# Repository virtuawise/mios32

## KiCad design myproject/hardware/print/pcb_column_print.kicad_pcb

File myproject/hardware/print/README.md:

# 1:1 test prints – check the real parts before ordering

Generated by `make_print_parts.py` (KiCad's Python) and `make_spacers.py` from the real board files, so every hole is
where the ordered PCBs will have it.

| File | What | Print |
|---|---|---|
| `pcb_left.stl`, `pcb_column.stl` | PCB stand-ins with all holes (switch pins, encoder lugs, LED, OLED header, stack holes) | 1.6 mm |
| `plate_left.stl`, `plate_column1.stl` | switch plate section | 1.6 mm as exported; **scale Z to 1.5 mm** (MX clips are made for 1.5) |
| `front_left.stl`, `front_column1.stl` | front panel section (cut-outs; legends are only print on the real panel) | 1.6 mm |
| `spacer_3.5mm.stl` | PCB -> plate (print 4 per section) | |
| `spacer_5.0mm.stl` | plate -> front panel (the 5 mm Würth standoff) | |

Sections: left block (panel x 0-103.2 mm) and column 1 (x 103.2-194.2 mm), cut in the gaps between the groups.
Stack: PCB stand-in, 3.5 mm spacers, plate, 5.0 mm spacers, front panel, held with M2 screws (or pins) through the
2.2 mm stack holes.

What to check with the real parts (the VERIFY items of `../README.md`):
1. MX switches clip into the plate and sit straight; the 18 mm caps move freely in the front cut-outs (1 mm around).
2. MEC 3FTH9: the 4 switch pins **and the 2 LED pins** go into the holes (LED pin positions are read from the drawing).
   The 1T cap moves freely in the 11 x 11 mm hole and sticks out ~3.3 mm.
3. EC11E: pins and lugs fit, the shaft is centred in the 7.5 mm hole, the body passes the plate.
4. Newhaven: pins in the header row, 2.5 mm spacer below it, glass just under the front panel, active area centred in
   the window.
5. Cap heights: how far the big caps stick out (expected ~8 mm with an 18 mm cap; lower profile if too high).

The PCB stand-ins have **enlarged holes** (every pin hole +0.6 mm, at least 1.8 mm; MX pegs 2.3 mm) so the pins can be
pushed through by hand – the real PCBs keep the datasheet sizes. Other FDM holes come out ~0.1-0.2 mm small: use the slicer's hole compensation (e.g. "XY hole compensation 0.15 mm") or the
fit is tighter than on the real FR4 parts.

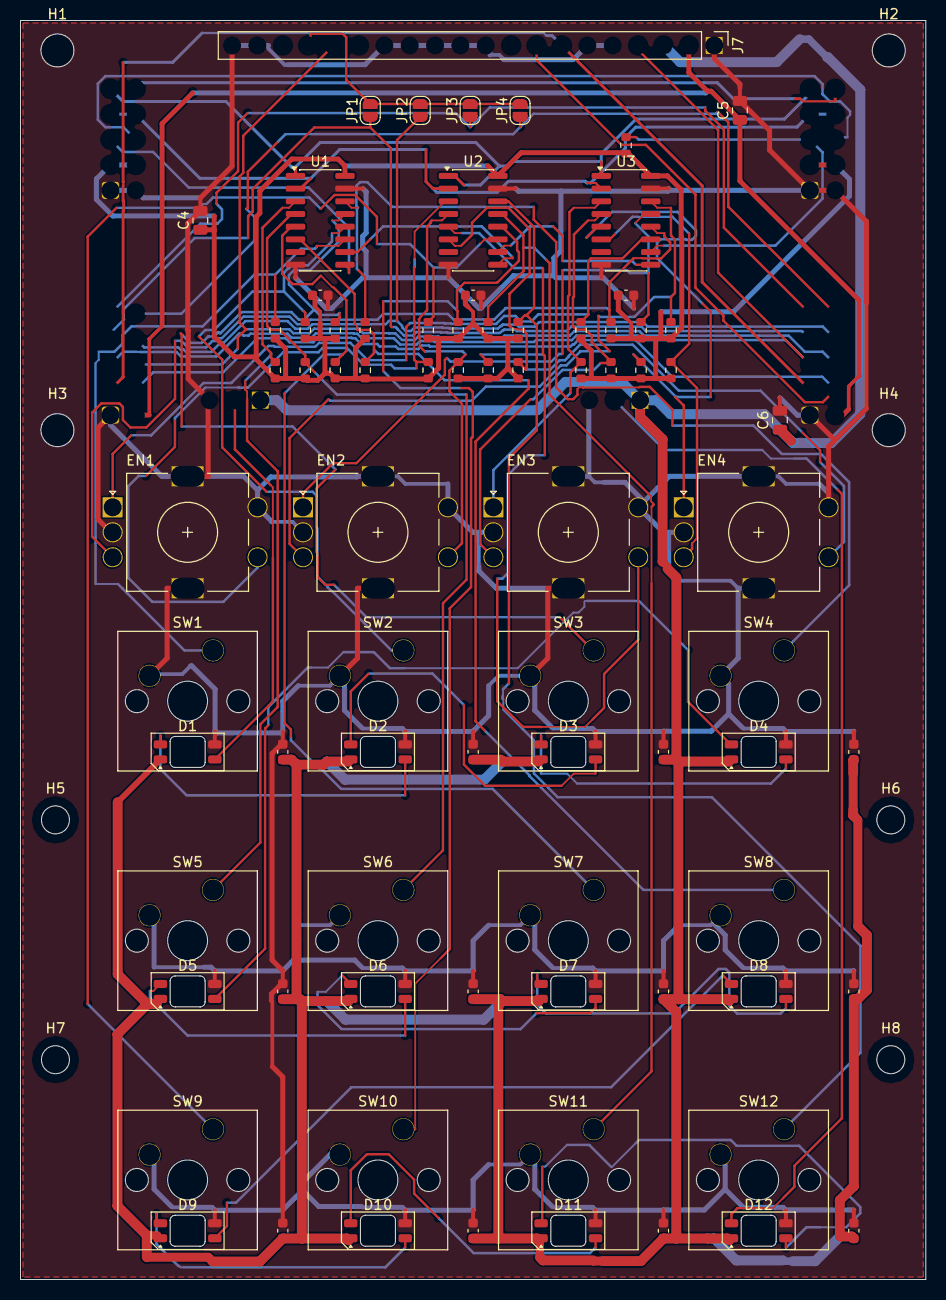
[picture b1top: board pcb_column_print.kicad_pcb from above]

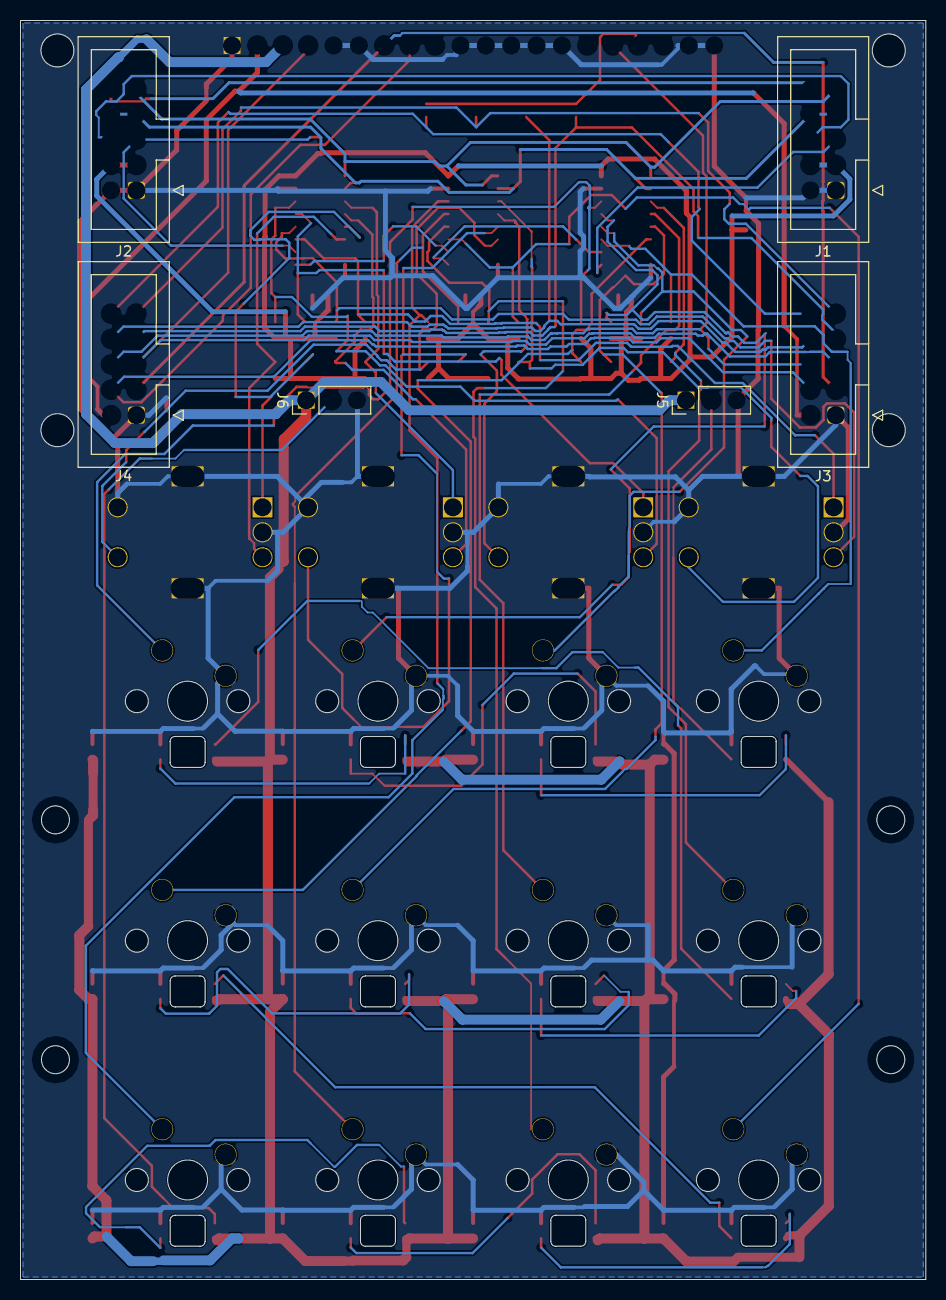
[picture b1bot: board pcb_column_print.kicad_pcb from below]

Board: 2 copper layers, 90.6 x 126.0 mm, 93 parts (6 on the bottom side), 58 nets.

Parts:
C1, C2, C3: 100nF; C_0603_1608Metric
C4, C5: 10uF; C_0805_2012Metric
C6: 22uF; C_0805_2012Metric
CL1, CL2, CL3, CL4, CL5, CL6, CL7, CL8, CL9, CL10, CL11, CL12: 100nF; C_0603_1608Metric
D1, D2, D3, D4, D5, D6, D7, D8, D9, D10, D11, D12: SK6812MINI-E; LED_SK6812MINI-E_ReverseMount_Cut3.5x3.1
EN1, EN2, EN3, EN4: EC11E; RotaryEncoder_Alps_EC11E-Switch_Vertical_H20mm
H1, H2, H3, H4: MountingHole_2.7mm_M2.5
H5, H6, H7, H8: MountingHole_2.2mm_M2
J1: SRIO_UP; IDC-Header_2x05_P2.54mm_Vertical
J2: SRIO_DN; IDC-Header_2x05_P2.54mm_Vertical
J3: OLED_BUS_IN; IDC-Header_2x05_P2.54mm_Vertical
J4: OLED_BUS_OUT; IDC-Header_2x05_P2.54mm_Vertical
J5: LED_IN; PinHeader_1x03_P2.54mm_Vertical
J6: LED_OUT; PinHeader_1x03_P2.54mm_Vertical
J7: NHD-3.12-25664UCY2; PinHeader_1x20_P2.54mm_Vertical
JP1: CS0; SolderJumper-2_P1.3mm_Open_RoundedPad1.0x1.5mm
JP2: CS1; SolderJumper-2_P1.3mm_Open_RoundedPad1.0x1.5mm
JP3: CS2; SolderJumper-2_P1.3mm_Open_RoundedPad1.0x1.5mm
JP4: CS3; SolderJumper-2_P1.3mm_Open_RoundedPad1.0x1.5mm
R1, R2, R3, R4, R5, R6, R7, R8, R9, R10, R11, R12, R13, R14, R15, R16, R17, R18, R19, R20, R21, R22, R23, R24, R25: 10k; R_0603_1608Metric
SW1: KEY_GP1; SW_Cherry_MX_1.00u_PCB
SW2: KEY_GP2; SW_Cherry_MX_1.00u_PCB
SW3: KEY_GP3; SW_Cherry_MX_1.00u_PCB
SW4: KEY_GP4; SW_Cherry_MX_1.00u_PCB
SW5: KEY_SEL1; SW_Cherry_MX_1.00u_PCB
SW6: KEY_SEL2; SW_Cherry_MX_1.00u_PCB
SW7: KEY_SEL3; SW_Cherry_MX_1.00u_PCB
SW8: KEY_SEL4; SW_Cherry_MX_1.00u_PCB
SW9: KEY_FN1; SW_Cherry_MX_1.00u_PCB
SW10: KEY_FN2; SW_Cherry_MX_1.00u_PCB
SW11: KEY_FN3; SW_Cherry_MX_1.00u_PCB
SW12: KEY_FN4; SW_Cherry_MX_1.00u_PCB
U1, U2, U3: 74HC165; SOIC-16_3.9x9.9mm_P1.27mm

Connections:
+3V3: C5.1, J3.2, J4.2, J7.2
+5V: C1.1, C2.1, C3.1, C4.1, J1.3, J1.4, J2.3, J2.4, R1.1, R2.1, R3.1, R4.1, R5.1, R6.1, R7.1, R8.1, R9.1, R10.1, R11.1, R12.1, R13.1, R14.1, R15.1, R16.1, R17.1, R18.1, R19.1, R20.1, R21.1, R22.1, R23.1, R24.1, R25.1, U1.16, U2.16, U3.16
CS0: J3.7, J4.7, JP1.1
CS1: J3.8, J4.8, JP2.1
CS2: J3.9, J4.9, JP3.1
CS3: J3.10, J4.10, JP4.1
ENC1_A: EN1.A, R17.2, U3.11
ENC1_B: EN1.B, R18.2, U3.12
ENC1_P: EN1.S1, R13.2, U2.3
ENC2_A: EN2.A, R19.2, U3.13
ENC2_B: EN2.B, R20.2, U3.14
ENC2_P: EN2.S1, R14.2, U2.4
ENC3_A: EN3.A, R21.2, U3.3
ENC3_B: EN3.B, R22.2, U3.4
ENC3_P: EN3.S1, R15.2, U2.5
ENC4_A: EN4.A, R23.2, U3.5
ENC4_B: EN4.B, R24.2, U3.6
ENC4_P: EN4.S1, R16.2, U2.6
GND: C1.2, C2.2, C3.2, C4.2, C5.2, C6.2, CL1.2, CL2.2, CL3.2, CL4.2, CL5.2, CL6.2, CL7.2, CL8.2, CL9.2, CL10.2, CL11.2, CL12.2, D1.3, D2.3, D3.3, D4.3, D5.3, D6.3, D7.3, D8.3, D9.3, D10.3, D11.3, D12.3, EN1.C, EN1.MP, EN1.S2, EN2.C, EN2.MP, EN2.S2, EN3.C, EN3.MP, EN3.S2, EN4.C, EN4.MP, EN4.S2, J1.1, J1.2, J2.1, J2.2, J3.1, J4.1, J5.3, J6.3, J7.1, J7.5, J7.6, J7.10, J7.11, J7.12, J7.13, J7.14, J7.19, J7.20, SW1.2, SW2.2, SW3.2, SW4.2, SW5.2, SW6.2, SW7.2, SW8.2, SW9.2, SW10.2, SW11.2, SW12.2, U1.8, U1.15, U2.8, U2.15, U3.8, U3.15
KEY_FN1: R9.2, SW9.1, U2.11
KEY_FN2: R10.2, SW10.1, U2.12
KEY_FN3: R11.2, SW11.1, U2.13
KEY_FN4: R12.2, SW12.1, U2.14
KEY_GP1: R1.2, SW1.1, U1.11
KEY_GP2: R2.2, SW2.1, U1.12
KEY_GP3: R3.2, SW3.1, U1.13
KEY_GP4: R4.2, SW4.1, U1.14
KEY_SEL1: R5.2, SW5.1, U1.3
KEY_SEL2: R6.2, SW6.1, U1.4
KEY_SEL3: R7.2, SW7.1, U1.5
KEY_SEL4: R8.2, SW8.1, U1.6
LED_D1: D1.2, D2.4
LED_D2: D2.2, D3.4
LED_D3: D3.2, D4.4
LED_D4: D4.2, D5.4
LED_D5: D5.2, D6.4
LED_D6: D6.2, D7.4
LED_D7: D7.2, D8.4
LED_D8: D8.2, D9.4
LED_D9: D9.2, D10.4
LED_D10: D10.2, D11.4
LED_D11: D11.2, D12.4
LED_IN: D1.4, J5.2
LED_OUT: D12.2, J6.2
OLED_CS: J7.17, JP1.2, JP2.2, JP3.2, JP4.2
OLED_DC: J3.5, J4.5, J7.4
OLED_RES: J3.6, J4.6, J7.16
OLED_SCLK: J3.3, J4.3, J7.7
OLED_SDIN: J3.4, J4.4, J7.8
RC1: J1.10, J2.10
RC2: J1.9, J2.9, U1.1, U2.1, U3.1
SC: J1.7, J1.8, J2.7, J2.8, U1.2, U2.2, U3.2
SI_DN: J2.5, R25.2, U3.10
SI_UP: J1.5, U1.9
SO: J1.6, J2.6
SR_12: U1.10, U2.9
SR_23: U2.10, U3.9
VLED: C6.1, CL1.1, CL2.1, CL3.1, CL4.1, CL5.1, CL6.1, CL7.1, CL8.1, CL9.1, CL10.1, CL11.1, CL12.1, D1.1, D2.1, D3.1, D4.1, D5.1, D6.1, D7.1, D8.1, D9.1, D10.1, D11.1, D12.1, J5.1, J6.1, J7.3

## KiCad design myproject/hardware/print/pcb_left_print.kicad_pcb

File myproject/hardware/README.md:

# Hardware – front panel PCBs (design, step 1: block diagram and connections)

Status: **design, nothing ordered or routed yet.** Every connection below is checked against a named source;
items marked **VERIFY** still have to be checked before the schematic is final.

## Principle (as Wilba / MIDIbox)
Wilba's MB-SEQ front panel (hwcfg `apps/sequencers/midibox_seq_v4/hwcfg/wilba/MBSEQ_HW.V4`) uses the MIDIbox SRIO chain:
one 8x8 button matrix on 1 DIN register, one 8x8 LED matrix on 2 DOUT registers (select + LEDs), encoders directly on
DIN registers (2 pins each, `DETENTED3`), 23 shift registers in one chain on J8/J9 of the core. The LCDs hang on J15.

We keep the same building blocks (74HC165 DIN / 74HC595 DOUT on J8/J9, the same `MBSEQ_HW.V4` mechanism, displays on
J15), with two differences, both for modularity:
- **No button matrix across modules.** Each module has its own 74HC165 registers in the chain (like MBHP_DINX4): no
  diodes, no ghosting, identical modules. (Wilba's matrix saves chips but needs all 8 select lines on every board.)
- **Big-key LEDs are SK6812 (WS2812 compatible)** on one data line instead of an LED matrix (MIOS32 `modules/ws2812`,
  TIM4 + DMA on **PB6 = J4B.SC**; used in NG, CV v2, SEQ v4 Lite – not yet in the SEQ v4 firmware).

## Modules
| PCB | Qty | Content | DIN inputs | 
|---|---|---|---|
| Column PCB (~91 x 110 mm) | 4 (identical) | 1 OLED display (Newhaven NHD-3.12-25664UC: display glass on its own small PCB, plugged in with its 1x20 header and screwed on with its 4 M2.5 holes – one part, no extra board), 4 EC11E with push, 12 MX keys (GP, select, function row), 12 SK6812MINI-E | 4 x 2 (A/B) + 4 push + 12 keys = 24 -> **3 x 74HC165** |
| Left PCB (100.3 x 126 mm) | 1 | datawheel EC11E with push, 13 MEC 3FTH9 small keys (LED fitted by APEM), 5 MX transport keys + 5 SK6812MINI-E, beat LED; interface to the core (SRIO, J15A, J4B) and the 5 V LED/OLED supply input | 2 + 1 + 13 + 5 = 21 -> 3 x 74HC165; LEDs 13 + 1 -> 2 x 74HC595 |
| Switch plate | 1 | 1.5 mm FR4 or aluminium, 14 x 14 mm MX cut-outs, holds the switches and the encoders' alignment | – |
| Front plate | 1 | aluminium 2-3 mm, one cut-out per key row, holes for small keys / encoders / OLED windows | – |

Totals: 15 DIN + 2 DOUT registers (SEQ limit `SRIO_NUM_SR` 23 – OK). 53 RGB LEDs (48 + 5) on one WS2812 line.

## Connections (verified)
**Core J8/J9 (SRIO, 2x5 box header)** – source: `ucapps.de/mbhp/mbhp_core_stm32f4.pdf`, drawing of J8/9:
| Row | left column = **J9 (DIN chain)** | right column = **J8 (DOUT chain)** |
|---|---|---|
| 1 | Vs (GND) | Vs (GND) |
| 2 | Vd (+5 V) | Vd (+5 V) |
| 3 | **SI** (serial in from the DIN chain = QH of the last 74HC165) | **SO** (serial out to DS of the first 74HC595) |
| 4 | SC (shift clock) | SC (shift clock) |
| 5 | **RC2** (load of the 74HC165s) | **RC1** (latch of the 74HC595s) |
5 V level. **VERIFY**: which corner is pin 1 on the core PCB (silkscreen) before drawing the connector footprint.
Chaining as MBHP_DINX4 (`ucapps.de/mbhp/mbhp_dinx4.pdf`): QH of each 74HC165 to SER of the previous one, 10 k pull-ups on
all inputs, 100 nF per IC.

**OLEDs on J15** – source: `modules/app_lcd/ssd1322/app_lcd.c`, `mios32/STM32F4xx/mios32_board.c`:
| Signal | Core | Remark |
|---|---|---|
| SCLK | J15 E1 (PC8) and E2 (PC9) | `J15_PIN_SERLCD_SCLK` drives both |
| SDIN | J15 RW (PC11) | `J15_PIN_SERLCD_DATAOUT` |
| D/C | J15 RS (PA8) | `MIOS32_BOARD_J15_RS_Set` |
| CS0..CS3 | J15 D0..D3 | outputs of a 74HC595 on the core (RW also drives its OE#) |
3.3 V push-pull (`APP_LCD_OUTPUT_MODE 0`). Firmware: the driver currently always selects CS0 (`u8 cs=0; // TODO`) –
has to be extended for 4 displays. **VERIFY**: SSD1322 serial mode pins on the Newhaven module (BS0/BS1 jumpers for
4-wire SPI), reset line.

**SK6812 chain** – source: `modules/ws2812/ws2812.c`: data from **PB6 (J4B.SC)**, 800 kHz. 3.3 V data into a 5 V LED
(VIH 0.7 x VDD = 3.5 V): use a **74AHCT125 level shifter** at the start of the chain.
**SK6812MINI-E pinout (datasheet REV02, Adafruit 4960): 1 = VDD, 2 = DOUT, 3 = GND, 4 = DIN.** The KiCad symbol
`SK6812MINI-E` inherits the older SK6812 numbering (1 VSS, 2 DIN, 3 VDD, 4 DOUT) – **do not use it**; pads are wired
from the datasheet. **VERIFY** pad positions of the reverse-mount footprint against the datasheet drawing (mirrored).

**OLED (Newhaven NHD-3.12-25664UCY2, yellow) in 4-wire SPI** – source: datasheet rev. 7, p. 4-8: BS1 = BS0 = GND
(pins 19/20); 7 = SCLK (D0), 8 = SDIN (D1), 9 (D2) open, 4 = D/C, 16 = /RES, 17 = /CS, 5-6 and 10-14 GND, 2 = VDD 3.3 V,
1 = VSS, 3/15/18 not connected.

**Encoders** – EC11E footprint `RotaryEncoder_Alps_EC11E-Switch_Vertical_H20mm`: pads A, B, C (common), S1/S2 (push),
MP (mounting). As Wilba: A and B on two DIN inputs, C to GND, push on a third DIN input.

## Power
53 SK6812 at full white ~3.2 A – limit brightness in firmware and/or feed the LED rail from a separate 5 V supply, not
through the ribbon cables. OLEDs ~3.3 V, Newhaven module current per datasheet (**VERIFY**).

## Mechanics
- **Stack (bottom to top):** key PCB (switches, LEDs, encoders, ICs) -> **switch plate** 5 mm above it (plain FR4 1.5/1.6 mm,
  not visible, holds the MX switches) -> **front panel** = printed FR4 PCB, matte black solder mask with white silkscreen
  legends (printed, not engraved), at about the height of the top of the switch housings -> caps.
  **Only the caps come through the front panel**: one cut-out per key row (caps move down into it when pressed), windows for
  the OLEDs, holes for encoder shafts and the small MEC caps. **VERIFY** with the chosen switch: housing height above the plate
  (~6.6 mm for Cherry MX), cap clearance over the 4 mm travel, encoder shaft length through the panel + knob, OLED glass
  height behind the window.
- **Fastening without visible screws:** SMD threaded standoffs (e.g. Würth SMSN, M2.5/M3) reflowed on the back of the front
  panel PCB, spacers down to the switch plate and the key PCB, screws from below; the case is fixed the same way. Spread around each screen group
  and between the rows. Encoders without a nut on the front.
- **No visible fasteners on the front.** The OLED displays (Newhaven, glass on its own small PCB) are plugged into and screwed to their column PCB; switches clip into the switch
  plate; encoders are held by the PCB/plate; the front plate is fixed from behind (press-in threaded studs / bushings).
- The rigidity comes from the switch plate + front plate; every module PCB is fixed with >= 4 standoffs.
- Board interconnect: keyed, latching ribbon (IDC) for SRIO + OLED bus; separate wires for the LED 5 V rail.

## Next steps
1. Schematic of the column PCB in KiCad (symbols with the checked pinouts), ERC.
2. Placement on the panel grid (91 mm groups, 19.05 mm keys), board outline, mounting holes; render and compare with the
   virtual panel.
3. Routing (Freerouting), DRC, review against this list; then the left PCB; Gerbers/BOM/CPL.

## Column PCB – status (step 2: parts, connections, placement)
`column/build_column.py` builds `column/column.kicad_pcb` (KiCad 10, Python API): 93 footprints, 58 nets, placement on the
panel grid (keys 19.05 mm, rows 24 mm, OLED header and M2.5 holes per the Newhaven drawing, M3 holes for the panel stack).
`column/verify_column.py` reads the saved board back and checks **every pad** against the expected nets plus independent
datasheet rules (74HC165 power/control, SK6812MINI-E VDD/GND, Newhaven serial pins, core J8/J9 pinout), the unbroken LED
chain and the DIN chain -> **293 pads + 72 rules OK**. KiCad DRC: no errors except 12 intended courtyard overlaps
(LED under its switch). Not routed yet (235 unconnected items).
Findings while checking: the KiCad symbol `SK6812MINI-E` has the wrong pin numbering for this part (we wire per datasheet);
KiCad's reverse-mount footprint has only 0.17 mm pad-to-cut-out -> own footprint `lib/seq4oled.pretty/LED_SK6812MINI-E_ReverseMount_Cut3.5x3.1`
(0.30 mm; **VERIFY** the manufacturer's inner router radius <= 0.5 mm). Renders: `column/render_top.png`, `column/render_bottom.png`.
Input mapping (for MBSEQ_HW.V4): U1 D0-3 GP keys 1-4, D4-7 select keys 1-4; U2 D0-3 function keys 1-4, D4-7 encoder pushes 1-4;
U3 D0/D1 encoder 1 A/B ... D6/D7 encoder 4 A/B. CS select: solder one of JP1..JP4 per board position.

## Grounding (no ground loops)
- **On the column PCB:** one GND net, poured on both layers (F.Cu + B.Cu, 0.3 mm clearance, islands removed), tied together
  by a 7.5 mm grid of stitching vias plus extra vias in every plane piece that had fewer than 2 links (64 stitching vias).
  Pieces that still hang on one point are small slivers between tracks. Connector and encoder GND pins have a full
  (not thermal) connection, so return current between boards sees low impedance. A plane is one node, so a loop *on* the board does not exist.
- **Between boards:** star from the core, no ring. Each module gets GND only through its own SRIO cable (2 GND pins),
  the OLED cable (GND next to every clock) and the LED cable (GND next to VLED, as a twisted pair from the LED supply). The
  module-to-module chaining cables (J2 -> next J1) also carry GND: that is a loop between modules, but its area is the
  cable itself (GND runs right next to the signals), so no field can couple into it – this is the normal MIDIbox DINX4 practice.
  **Do not** add extra ground wires between modules or to the case beyond the cables.
- **LED supply:** separate 5 V for the SK6812 rail; its GND joins the logic GND at **one point** (the core / power input), so
  the ~3 A LED current does not flow through the SRIO ribbons.
- **Case:** FR4 front panel and switch plate are insulators (their standoffs tie nothing). With a metal case: connect the case to
  GND at one point only, at the power inlet. MIDI IN is opto-isolated (no ground connection to other gear); USB brings the
  computer's ground – if hum appears through audio gear, use a USB isolator, not a ground lift.

## Left PCB – status (built, routed, verified)
`left/build_left.py` -> `left/left.kicad_pcb`, routed with `./route.sh left` (same pipeline as the column: build -> Specctra ->
Freerouting -> `route_board.py` (GND planes, stitching, no one-layer vias) -> `verify_left.py` -> DRC).
Result: **366 pads + 140 datasheet rules OK**, DRC 0 unconnected, only the 5 intended LED-under-switch courtyard overlaps.
- **Small keys: APEM Multimec 3FTH9xx** – the LED is fitted by APEM, the colour is in the part number (65 white, 40 yellow
  for the amber keys, 80 red for Rec.). Own footprint `lib/seq4oled.pretty/SW_MEC_3FTH9_LED` from the datasheet
  (MEC-MULTIMEC3F-2203 p. 3, "TH illuminated"): contact 1/2 to 3/4 on a 10.16 x 7.62 mm grid, LED K in the left column 2.54 mm
  below pin 2, LED A in the right column 2.54 mm above pin 3. **VERIFY** the LED pin positions with a real switch (read from
  the drawing, no table) and the PCB thickness (datasheet 1.4 +- 0.2 mm -> order 1.6 mm).
- **DIN (first in the chain, SR 1-3)**: U1 D0-D7 = Step, Track, Param, Trigger, Instr., Mute, Phrase, Bookm.; U2 = Solo, Metr.,
  Loop, Rec., Live, Rew, Fwd, Stop; U3 = datawheel A/B (D0/D1, same register as MIOS32 requires), datawheel push, Play,
  Pause, 3 spare (pulled up). Column modules follow as SR 4-6, 7-9, 10-12, 13-15.
- **DOUT (only here, SR 1-2)**: U4 QA-QH = LEDs Step ... Bookm.; U5 QA-QF = Solo, Metr., Loop, Rec., Live, Beat. As MBHP_DOUTX4:
  output -> 680 R -> LED -> GND (~4 mA, 14 LEDs on 2 registers).
- **Core cables**: J1 = core J8/J9 (2x5), J3 = core **J15A** (2x8: 1 Vs, 2 Vd, 3 V0, 4 RS, 5 RW, 6 E, 7-14 D0-D7, 15/16 B+/B-,
  from the MBHP_CORE_STM32F4 schematic) – only RS/RW/E/D0-D3 and Vs are used, **Vd is not connected**; J5 = core **J4B**
  (2x5: pin 6 = SC = PB6, odd pins + 2/4 = Vs) for the RGB LED data.
- **OLED reset**: MCP100-300 supervisor (SOT-23: 1 /RST, 2 VDD, 3 VSS, Microchip DS11187F) holds /RES of all 4 displays low
  until 3.3 V is stable + 350 ms (J15 has no reset line). **VERIFY** SOT-23 pin 1 = /RST against the current datasheet.
- **LED data**: 74AHCT1G125 buffer (TTL input takes the open-drain PB6 with the core's 2.2 k pull-up to 5 V, `modules/ws2812`),
  33 R series resistor, then D1-D5 and on to column 1 (J6 -> column J5).

## Power (revised after reading the Newhaven datasheet, p. 6/7)
- **Newhaven in jumper option #1**: on every display move the 0 R from **R14 to R15**. Then the boost converter runs from
  BC_VDD (pin 3) = 5 V: **150 mA typ / 170 mA max at 100 % on**, and VDD (pin 2) 3.3 V only feeds the logic (200 uA).
  Default jumper would need 310/340 mA *from 3.3 V* per display (1.4 A for four) – too much for the core.
  The column PCB connects pin 3 to VLED; with the default jumper pin 3 is open on the module, so nothing breaks.
- **One 5 V supply for LEDs + OLED boost** (J7 on the left PCB, JST VH): 58 SK6812 + 4 x 170 mA; >= 4 A PSU, brightness
  limited in firmware. Its GND meets the logic GND only on the left PCB (single point, see Grounding).
- **OLED logic 3.3 V**: AP2112K-3.3 on the left PCB from the core's 5 V (a few mA).
- **Core J15_S jumper must be set to 3.3 V**: the core's 74HC595 that drives CS0-3 is powered from it; at 5 V the CS lines
  would exceed the SSD1322's VIH max (= VDD).

## Firmware for the new hardware (built, host-tested; not yet on real OLED/RGB hardware)
- **Hardware config**: `hardware/MBSEQ_HW.V4`, generated by `hardware/make_hwcfg.py` from the PCB mapping (every DIN pin used
  once, checked by the script). Copy it to the SD card only when the new front panel is connected – on the current Wilba
  hardware it would switch J15 to the OLEDs and remap all buttons.
  New keywords: `OLED_SSD1322 <0..4>`, `OLED_CONTRAST <0..255>`, `RGBLED_ENABLED <0/1>`, `RGBLED_BRIGHTNESS <1..255>`.
- **OLEDs** (`core/seq_oled_hw.c`): the same 64x64 cells that go to the virtual panel are written to the 4 SSD1322 (column
  window of 16 x 4 pixels per cell, CS0-3 on J15 D0-D3). Own bit-bang at ~8 MHz (SSD1322 SCLK cycle >= 100 ns) over the
  ribbon cables. With `OLED_SSD1322` set, the character LCD output to J15 (`SEQ_LCD_Update`, special chars, logo) is off.
  Host test `tools/oled_hw_test/run.sh`: an SSD1322 emulator receives the SPI bytes and checks init + all 16 cells -> OK.
  Init sequence = Newhaven's NHD-3.12 example values (**VERIFY** on the first display: nibble order (remap 0x14), contrast).
- **RGB key LEDs** (`core/seq_rgbled.c`, `modules/ws2812`, PB6 = J4B.SC): the SEQ keeps driving its LEDs as before; in the
  hwcfg the big-key LEDs sit on DOUT registers 3-9 that are not fitted, and seq_rgbled reads them back every 20 ms and
  colours the chain: GP amber (play position warm white), select keys amber/warm white as the virtual panel, function row
  amber, Play sage green, other transport keys warm white; brightness from the hwcfg (default 64/255 = 25 %).
- **Note on J15**: the core's J15 RW line is also OE# of its 74HC595 that drives CS0-3, so the CS lines float while a "1"
  bit is clocked. The OLED bus keeps CS0-3 away from SCLK in the ribbon (pins 7-10 vs. 3) so they do not pick up the clock.

## Front panel + switch plate (built, verified against the PCBs)
`panel/build_panel.py` -> `panel/front.kicad_pcb` (474.7 x 144.4 mm, = the virtual panel) and `panel/plate.kicad_pcb`, both
from the panel_oled.html geometry. `panel/verify_panel.py` checks them **independently against the routed PCBs**: 53 MX keys
centred in 14.0 mm plate cut-outs with >= 0.9 mm free around every 18 mm cap in the front cut-outs, 13 small keys centred in
11.0 x 11.0 mm front holes (APEM cut-out for the 1T cap), 17 encoder shafts centred in their holes, 4 OLED active areas
inside their windows, 22 PCB stack holes with a plate hole and a front standoff above them, every tall top-side part under a
plate opening, every standoff >= 1 mm from cut-outs/holes/edge -> **OK**. DRC of both plates clean.
- **Front panel**: FR4 1.6 mm, **black solder mask, white silkscreen** (printed legends: select-mode/left-block keys, function
  row, transport symbols, DATA, BEAT, logo; no GP/select labels). OLED windows 80.0 x 21.0 mm (bezel opening 82 x 22).
- **No visible fasteners**: 30 Würth WA-SMSI **M1.6 bottom-closed** SMT spacers 97730506330R (L 5 mm, OD 3.3 mm, Würth only
  makes the closed version in M1.6; the M3 versions have a through hole or a locating hole) reflowed on the back.
  22 of them sit above the PCB stack holes: **one M1.6 screw per point from the back of the PCB** through the PCB, a 3.5 mm
  spacer tube, the switch plate, into the standoff – clamps PCB, plate and front panel at once. 8 more in the free margins
  (screwed from below the plate). PCB stack holes are unplated 2.2 mm with no copper within 2.5 mm: the screws never touch
  GND, so the mechanics add no ground connection between boards.
- **Switch plate**: FR4 1.5 mm, MX 14.0 x 14.0, 3F 10.8 x 10.8, one opening per column for the Newhaven module + encoders,
  datawheel 13 x 14, beat LED 3.6, 2.2 mm stack holes.

### Stack heights (z = 0 at the top of the key PCBs)
| Item | z (mm) | Source | Sticks out above the panel |
|---|---|---|---|
| Switch plate | 3.5 – 5.0 | MX plate mount: plate top 5.0 mm above the PCB (Cherry MX drawing) | – |
| Front panel | 10.0 – 11.6 | plate top + 5.0 mm standoff (97730506330R) + 1.6 mm FR4 | – |
| 3F + 1T cap (small keys) | top 14.9, travel 1 | APEM: 1T h = 14.9 mm, 3F travel 1 mm | **3.3 mm** (pressed 2.3) |
| MX housing | top 11.6 | plate + 6.6 mm (Cherry MX) | flush with the panel top |
| MX + 18 mm cap (big keys) | top ~19-20, travel 4 | cap height depends on the profile – **VERIFY with the sample caps** | ~8 mm (pressed ~4) |
| Newhaven glass | 2.5 – 8.5 | module 6.0 mm thick (datasheet), soldered on its pins over a 2.5 mm spacer | 1.5 mm below the panel back |
| EC11E15244G1 shaft ("20 mm") | top 24.5 | Alps drawing 5 (p.206): 4.5 mm body + 20 mm shaft above the mounting surface; bushing top ~11.5 | ~12.9 mm shaft for the knob (not 8.4) |
| Beat LED 3 mm | top ~10.3 | 5 mm LED spacer + 5.3 mm LED body – **VERIFY** (or a light pipe) | in the 3.2 mm hole |
Consequences already applied: the Newhaven is soldered directly (a 1x20 socket would put the glass at 14.5 mm, above the
panel), the 220 uF capacitor of the left PCB is on the back (7.7 mm tall). If the big caps stick out too far with the chosen
profile, use a lower profile (DSA/flat) rather than raising the panel – the small keys only have 3.3 mm.

## Case with AOUT / DOUT modules (gates, CV) – how it fits in
- **DOUT gate/trigger modules (MBHP_DOUTX4)**: in the same SRIO chain as the panel. The DOUT data (SO) runs core J8 ->
  left PCB (DOUT SR 1-2) -> through all 4 column PCBs unchanged -> **column 4, J2** (same 2x5 pinout as core J8/J9: GND,
  +5 V, SO, SC, RC1). A ribbon from there to the first DOUTX4 makes it DOUT SR 3, the next one SR 4, ...
  In the hwcfg: `DOUT_GATE_SR1 3` etc. SR 3-16 are free: the virtual registers for the RGB key LEDs sit at SR 17-23
  (`SRIO_NUM_SR 23`). Keep the whole chain short (< ~1 m of ribbon in total).
- **AOUT (MBHP_AOUT / AOUT_NG / AOUT_LC)**: on the core's **J19** (own SPI port) – nothing to do with the panel PCBs.
  Gates without a DOUT module: core **J5A/J5B** (`J5_ENABLED 1`). Both connectors stay free in this design.
- **Core connectors used by the panel**: J8/J9 (SRIO), J15A (OLEDs), J4B (RGB LED data, PB6). Still free: J19 (AOUT),
  J5A/B (gates), J4A (IIC), J11 (MIDI), J16 (SD), J10.
- **Power**: 5 V for logic + LEDs + OLED boost (>= 4 A) and +-12 V for the AOUT op-amps, e.g. one triple-output supply.
  Each rail gets its GND back to **one star point** (the 5 V LED input of the left PCB is that point for the panel).
- **Ground loops with a modular/synth**: CV/gate jacks on the rear panel with plastic (isolated) sockets, their ground
  only through the AOUT/DOUT module back to the star point; MIDI is opto-isolated; USB brings the computer's ground ->
  if a loop hums, a USB isolator, never a lifted ground. Metal case: tied to GND at one point, at the power inlet.
- **Mechanics**: everything hangs behind the front panel / switch plate; the PCBs have their IDC/power connectors on the
  back (about 9 mm). Core, AOUT and DOUT modules go on the case floor or the rear panel, ribbons to the left PCB (core)
  and to column 4 J2 (DOUT). Allow ~25 mm under the key PCBs for connectors and cables.

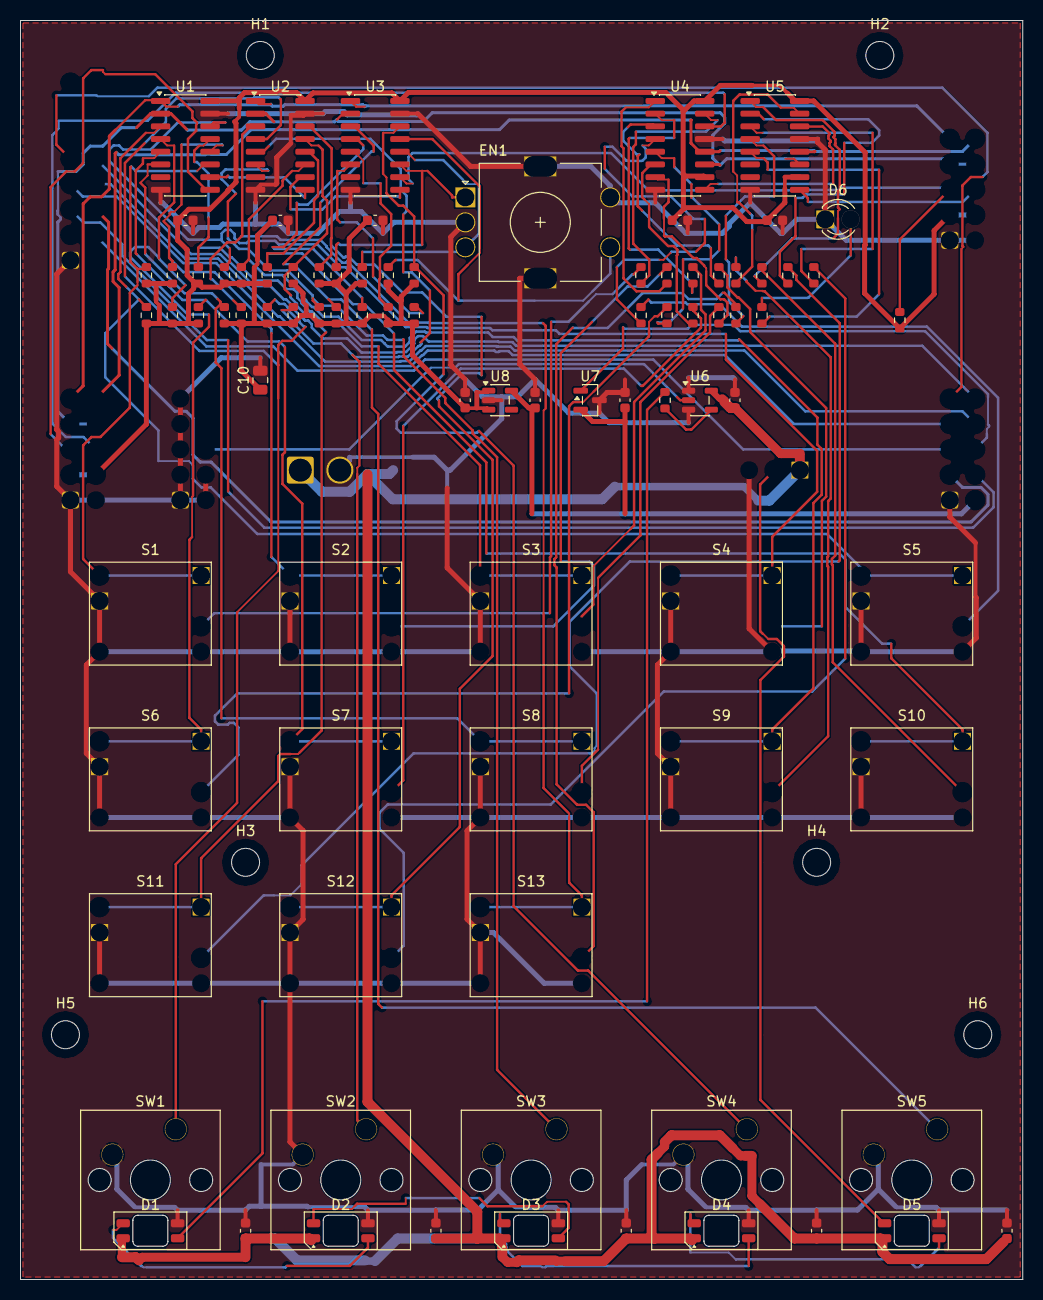
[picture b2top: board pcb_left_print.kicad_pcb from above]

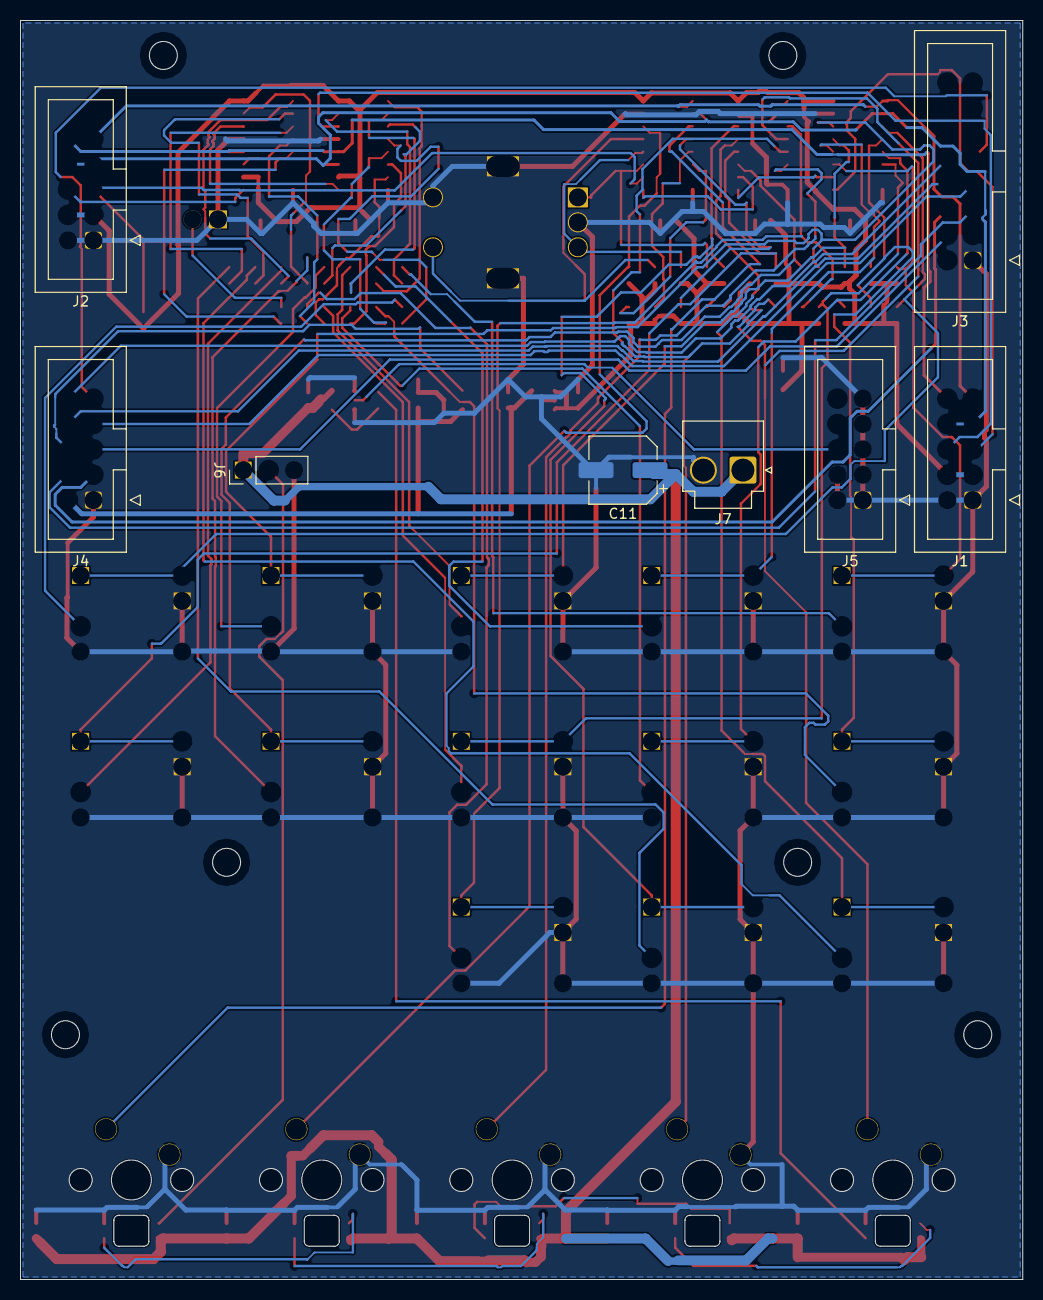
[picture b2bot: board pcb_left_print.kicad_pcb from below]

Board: 2 copper layers, 100.3 x 126.0 mm, 102 parts (8 on the bottom side), 82 nets.

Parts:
C1, C2, C3, C4, C5, C6, C7: 100nF; C_0603_1608Metric
C8, C9: 1uF; C_0603_1608Metric
C10: 10uF; C_0805_2012Metric
C11: 220uF 10V; CP_Elec_6.3x7.7
CL1, CL2, CL3, CL4, CL5: 100nF; C_0603_1608Metric
D1, D2, D3, D4, D5: SK6812MINI-E; LED_SK6812MINI-E_ReverseMount_Cut3.5x3.1
D6: 3mm red; LED_D3.0mm
EN1: EC11E; RotaryEncoder_Alps_EC11E-Switch_Vertical_H20mm
H1, H2, H3, H4, H5, H6: M1.6 stack; MountingHole_2.2mm_M2
J1: CORE_J8J9; IDC-Header_2x05_P2.54mm_Vertical
J2: SRIO_TO_COLUMN; IDC-Header_2x05_P2.54mm_Vertical
J3: CORE_J15A; IDC-Header_2x08_P2.54mm_Vertical
J4: OLED_BUS_OUT; IDC-Header_2x05_P2.54mm_Vertical
J5: CORE_J4B; IDC-Header_2x05_P2.54mm_Vertical
J6: LED_OUT; PinHeader_1x03_P2.54mm_Vertical
J7: 5V_LED_IN; JST_VH_B2P-VH_1x02_P3.96mm_Vertical
R1, R2, R3, R4, R5, R6, R7, R8, R9, R10, R11, R12, R13, R14, R15, R16, R17, R18, R19, R20, R21, R22, R23, R24, R39: 10k; R_0603_1608Metric
R25, R26, R27, R28, R29, R30, R31, R32, R33, R34, R35, R36, R37, R38: 680; R_0603_1608Metric
R40: 33; R_0603_1608Metric
S1, S2, S3, S4, S5, S6, S7, S8: 3FTH9+LED234 warm white; SW_MEC_3FTH9_LED
S9, S10, S11, S13: 3FTH9+LED234 yellow; SW_MEC_3FTH9_LED
S12: 3FTH9+LED234 red; SW_MEC_3FTH9_LED
SW1: KEY_REW; SW_Cherry_MX_1.00u_PCB
SW2: KEY_FWD; SW_Cherry_MX_1.00u_PCB
SW3: KEY_STOP; SW_Cherry_MX_1.00u_PCB
SW4: KEY_PLAY; SW_Cherry_MX_1.00u_PCB
SW5: KEY_PAUSE; SW_Cherry_MX_1.00u_PCB
U1, U2, U3: 74HC165; SOIC-16_3.9x9.9mm_P1.27mm
U4, U5: 74HC595; SOIC-16_3.9x9.9mm_P1.27mm
U6: 74AHCT1G125; SOT-23-5
U7: MCP100T-300; SOT-23
U8: AP2112K-3.3; SOT-23-5

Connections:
+3V3: C7.1, C9.1, J4.2, U7.2, U8.5
+5V: C1.1, C2.1, C3.1, C4.1, C5.1, C8.1, C10.1, J1.3, J1.4, J2.3, J2.4, R1.1, R2.1, R3.1, R4.1, R5.1, R6.1, R7.1, R8.1, R9.1, R10.1, R11.1, R12.1, R13.1, R14.1, R15.1, R16.1, R17.1, R18.1, R19.1, R20.1, R21.1, R22.1, R23.1, R24.1, R39.1, U1.16, U2.16, U3.16, U4.10, U4.16, U5.10, U5.16, U8.1, U8.3
CS0: J3.7, J4.7
CS1: J3.8, J4.8
CS2: J3.9, J4.9
CS3: J3.10, J4.10
DIN_SPARE1: R22.2, U3.4
DIN_SPARE2: R23.2, U3.5
DIN_SPARE3: R24.2, U3.6
DW_A: EN1.A, R17.2, U3.11
DW_B: EN1.B, R18.2, U3.12
DW_P: EN1.S1, R19.2, U3.13
GND: C1.2, C2.2, C3.2, C4.2, C5.2, C6.2, C7.2, C8.2, C9.2, C10.2, C11.2, CL1.2, CL2.2, CL3.2, CL4.2, CL5.2, D1.3, D2.3, D3.3, D4.3, D5.3, D6.1, EN1.C, EN1.MP, EN1.S2, J1.1, J1.2, J2.1, J2.2, J3.1, J4.1, J5.1, J5.2, J5.3, J5.4, J5.5, J5.7, J5.9, J6.3, J7.2, S1.3, S1.4, S1.5, S2.3, S2.4, S2.5, S3.3, S3.4, S3.5, S4.3, S4.4, S4.5, S5.3, S5.4, S5.5, S6.3, S6.4, S6.5, S7.3, S7.4, S7.5, S8.3, S8.4, S8.5, S9.3, S9.4, S9.5, S10.3, S10.4, S10.5, S11.3, S11.4, S11.5, S12.3, S12.4, S12.5, S13.3, S13.4, S13.5, SW1.2, SW2.2, SW3.2, SW4.2, SW5.2, U1.8, U1.15, U2.8, U2.15, U3.8, U3.15, U4.8, U4.13, U5.8, U5.13, U6.1, U6.3, U7.3, U8.2
KEY_BOOKM: R8.2, S8.1, S8.2, U1.6
KEY_FWD: R15.2, SW2.1, U2.5
KEY_INSTR: R5.2, S5.1, S5.2, U1.3
KEY_LIVE: R13.2, S13.1, S13.2, U2.3
KEY_LOOP: R11.2, S11.1, S11.2, U2.13
KEY_METRO: R10.2, S10.1, S10.2, U2.12
KEY_MUTE: R6.2, S6.1, S6.2, U1.4
KEY_PARAM: R3.2, S3.1, S3.2, U1.13
KEY_PAUSE: R21.2, SW5.1, U3.3
KEY_PHRASE: R7.2, S7.1, S7.2, U1.5
KEY_PLAY: R20.2, SW4.1, U3.14
KEY_REC: R12.2, S12.1, S12.2, U2.14
KEY_REW: R14.2, SW1.1, U2.4
KEY_SOLO: R9.2, S9.1, S9.2, U2.11
KEY_STEP: R1.2, S1.1, S1.2, U1.11
KEY_STOP: R16.2, SW3.1, U2.6
KEY_TRACK: R2.2, S2.1, S2.2, U1.12
KEY_TRIGGER: R4.2, S4.1, S4.2, U1.14
LEDA_BEAT: D6.2, R38.2
LEDA_BOOKM: R32.2, S8.6
LEDA_INSTR: R29.2, S5.6
LEDA_LIVE: R37.2, S13.6
LEDA_LOOP: R35.2, S11.6
LEDA_METRO: R34.2, S10.6
LEDA_MUTE: R30.2, S6.6
LEDA_PARAM: R27.2, S3.6
LEDA_PHRASE: R31.2, S7.6
LEDA_REC: R36.2, S12.6
LEDA_SOLO: R33.2, S9.6
LEDA_STEP: R25.2, S1.6
LEDA_TRACK: R26.2, S2.6
LEDA_TRIGGER: R28.2, S4.6
LEDQ_BEAT: R38.1, U5.5
LEDQ_BOOKM: R32.1, U4.7
LEDQ_INSTR: R29.1, U4.4
LEDQ_LIVE: R37.1, U5.4
LEDQ_LOOP: R35.1, U5.2
LEDQ_METRO: R34.1, U5.1
LEDQ_MUTE: R30.1, U4.5
LEDQ_PARAM: R27.1, U4.2
LEDQ_PHRASE: R31.1, U4.6
LEDQ_REC: R36.1, U5.3
LEDQ_SOLO: R33.1, U5.15
LEDQ_STEP: R25.1, U4.15
LEDQ_TRACK: R26.1, U4.1
LEDQ_TRIGGER: R28.1, U4.3
LED_BUF: R40.1, U6.4
LED_D1: D1.2, D2.4
LED_D2: D2.2, D3.4
LED_D3: D3.2, D4.4
LED_D4: D4.2, D5.4
LED_DATA_CORE: J5.6, U6.2
LED_IN: D1.4, R40.2
LED_OUT: D5.2, J6.2
OLED_DC: J3.4, J4.5
OLED_RES: J4.6, U7.1
OLED_SCLK: J3.6, J4.3
OLED_SDIN: J3.5, J4.4
RC1: J1.10, J2.10, U4.12, U5.12
RC2: J1.9, J2.9, U1.1, U2.1, U3.1
SC: J1.7, J1.8, J2.7, J2.8, U1.2, U2.2, U3.2, U4.11, U5.11
SI_DN: J2.5, R39.2, U3.10
SI_UP: J1.5, U1.9
SO: J1.6, U4.14
SO_DN: J2.6, U5.9
SR_12: U1.10, U2.9
SR_23: U2.10, U3.9
SR_45: U4.9, U5.14
VLED: C6.1, C11.1, CL1.1, CL2.1, CL3.1, CL4.1, CL5.1, D1.1, D2.1, D3.1, D4.1, D5.1, J6.1, J7.1, U6.5
